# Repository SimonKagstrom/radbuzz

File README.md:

# Radbuzz
Radbuzz is an infotainment and trip computer for electric mopeds and motorcycles, targeting VESC-based
controllers. It's built for an ESP32P4 microcontroller, but can also be run on the desktop for testing.

<p align="center">

</p>
<p align="center">

</p>
<p align="center">

</p>
<p align="center">

</p>

Features:

* OpenStreetMap-based map (currently OpenCycleMap) with different zoom levels, via a GPS module
* Supports receiving Google maps/OsmAnd/etc navigation instructions via the [Gadgetbridge](https://github.com/Freeyourgadget/Gadgetbridge) app
* Speedometer, both based on VESC data and GPS
* Trip data, with average consumption, distance etc
* Tesla-style power meter bar on the right
* Trip log shown on the map, with power indicator in color
* Range estimation shown on the map
* BMS status via BLE (currently em3ev KingShark/Ali new energy BMSes)
* Incoming phone calls can accepted/declined
* SMS:es and emails are forwarded from the phone
* A menu for configuration
* Written in clean and modern C++ (C++23)

Hardware:

* [Waveshare 4.3" ESP32P4 Touch](https://www.waveshare.com/product/arduino/boards-kits/esp32-p4/esp32-p4-wifi6-touch-lcd-4.3.htm)
* A rotary encoder
* UART-based GPS (UBLOX Neo-6M / Neo-7M tested)
* A CAN-bus adapter to communicate with the VESC (a Waveshare SN65HVD230 has been used)
* A DC/DC converter to power the ESP32P4 from the 12V outlet on the VESC (a [Waveshare DC-DC buck mini module](https://www.waveshare.com/dc5-36-to-dc3v3-5.htm) used here)

the pinout for the ESP32P4 can be seen in [waveshare_p4_touch_4_3/main.cc](esp32/waveshare_p4_touch_4_3/main/main.cc)

## Setup
First install the `eim` tool (the esp-idf installation manager).

```
eim install -i v6.1
source $HOME/.espressif/tools/activate_idf_v6.1.sh
npm i lv_font_conv -g
pip3 install jinja2 pyyaml
```

## Build (target)
```
cmake -GNinja -B radbuzz_waveshare_p4_touch_4_3 -DCMAKE_BUILD_TYPE=Release <path>/radbuzz/esp32/waveshare_p4_touch_4_3
cmake --build radbuzz_waveshare_p4_touch_4_3
```

And then flash with

```
cd radbuzz_waveshare_p4_touch_4_3
ninja flash   # Or idf.py flash
```

## Build (qt/unittest)
Install the same lvgl/Python dependencies as on target:

```
npm i lv_font_conv -g
pip3 install jinja2 pyyaml
```

And then:

```
cmake -GNinja -B radbuzz_qt <path>/radbuzz/qt
cmake --build radbuzz_qt
```

or

```
cmake -GNinja -B radbuzz_unittest <path>/radbuzz/test/unittest/
cmake --build radbuzz_unittest
```

See [doc/build_instructions.md](doc/build_instructions.md) for more details on building and flashing the C6
firmware for wifi/Bluetooth.

## The OSM API key
Get an API key for thunderforest via https://www.thunderforest.com/docs/apikeys/

Put this key as a plain string in an `osm_api_key.txt` file in the root directory of this
project, to build it into the firmware.

A key can also be placed on the SD card, as `app_data/osm_key.txt`, which will be
preferred over the build time one if it exists. It's JSON:

```json
{"api_key": "0123456789abcdef"}
```

## Wifi SSID
Store the SSIDs and passwords as JSON in an `app_data/ssid.txt` file on the SD card. E.g.,

```json
{
  "networks": [
    {"ssid": "MySsid", "password": "PasswordForMySsid"},
    {"ssid": "OtherSsid", "password": "PasswordForOtherSsid"},
    {"ssid": "OpenCafeSsid"}
  ]
}
```

Leave out the password for open networks. The networks are stored on the
board, and the file is only imported again when its contents change.

## Trip upload
Trips are uploaded to a [Traccar](https://www.traccar.org/) server with the OsmAnd protocol,
configured with a JSON `app_data/traccar.txt` file on the SD card:

```json
{"url": "https://host.tailnet.ts.net", "id": "device-id", "demo_id": "demo-device-id"}
```

The `demo_id` is optional, and demo trips are only uploaded with it. Like `ssid.txt`, the file
is stored on the board and only imported again when it changes.

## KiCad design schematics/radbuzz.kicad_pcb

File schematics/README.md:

## Setup for the mock script
```
pip3 install manifold3d trimesh matplotlib
```

## Generate a step file for import into onshape

```
kicad-cli pcb export step --subst-models \
    --component-filter "J1,J2,J3,J4,J5,J6,U2,C3,C14,C15,C16,C17" \
    --user-origin 42.775x113.55mm \
    -f -o radbuzz.step radbuzz.kicad_pcb
```

The component filter has no way to exclude a part, so the parts to include are
listed. J9 is left out, since it is the GPS module's header.

For the encoder board:

```
kicad-cli pcb export step --subst-models \
    --user-origin 36.25x76mm \
    -f -o encoder_board.step encoder_board/encoder_board.kicad_pcb
```

KiCad has no 3D model for the EC11E encoder, so the step file has only the
board and its connector, and kicad-cli warns about the missing model.

The user origin is the lower left corner of each board.

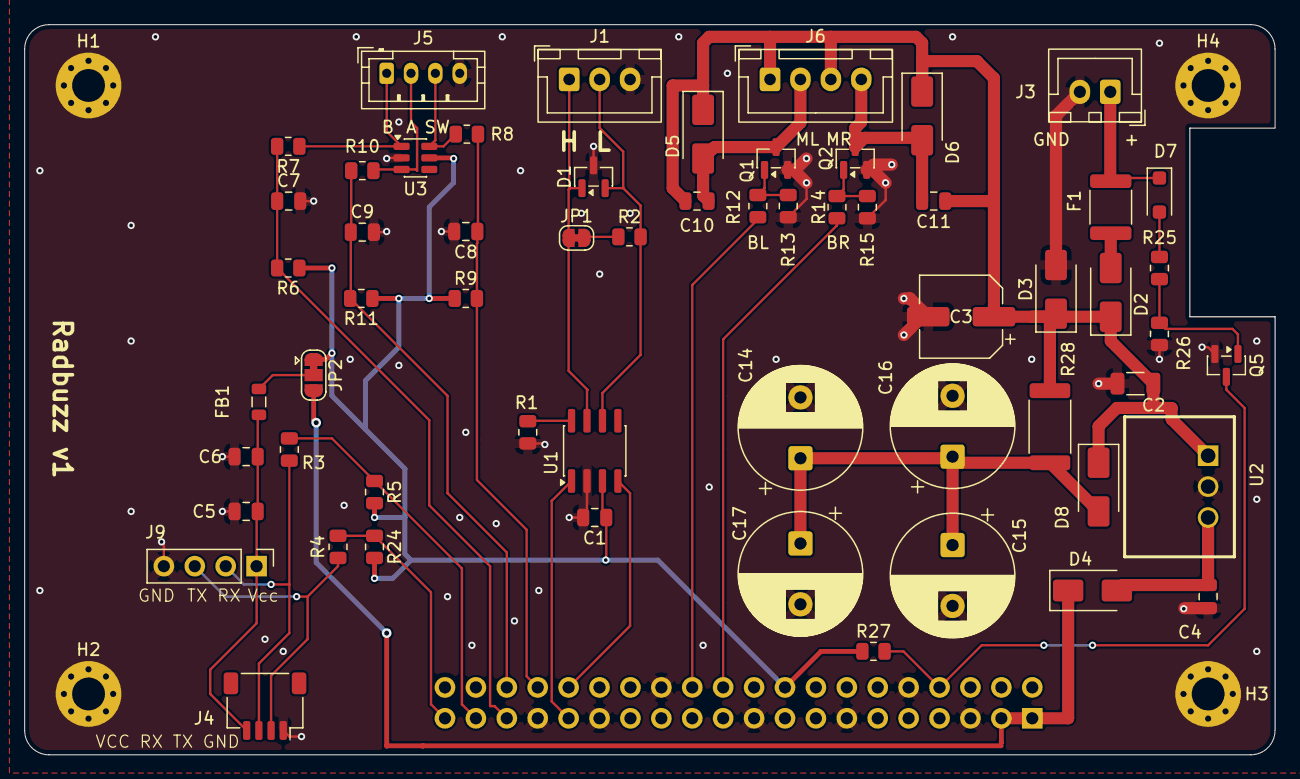
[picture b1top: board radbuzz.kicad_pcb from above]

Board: 2 copper layers, 102.8 x 60.0 mm, 64 parts (1 on the bottom side), 35 nets.

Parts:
C1, C6, C10, C11: 100nF; C_0805_2012Metric
C2: 10µF/50V X5R; C_1206_3216Metric
C3: 47µF/35V; CP_Elec_6.3x7.7
C4, C5: 22µF/25V X5R; C_0805_2012Metric
C7, C8, C9: 10nF; C_0805_2012Metric
C14, C15, C16, C17: 1000µF/35V; CP_Radial_D10.0mm_P5.00mm
D1: NUP2105L; SOT-23
D2, D4: SS34; D_SMA
D3: SMAJ15A; D_SMA
D5, D6, D8: SS14; D_SMA
D7: BZT52C9V1; D_SOD-123F
F1: Polyfuse 1.5A/24V; Fuse_1812_4532Metric
FB1: 600Ω@100MHz; L_0805_2012Metric
H1, H2, H3, H4: MountingHole_Pad; MountingHole_2.7mm_M2.5_Pad_Via
J1: CAN; JST_XH_B3B-XH-A_1x03_P2.50mm_Vertical
J2: BOARD; PinHeader_2x20_P2.54mm_Vertical
J3: POWER; JST_XH_B2B-XH-A_1x02_P2.50mm_Vertical
J4: GPS; JST_SH_SM04B-SRSS-TB_1x04-1MP_P1.00mm_Horizontal
J5: ROTARY_ENCODER; JST_PH_B4B-PH-K_1x04_P2.00mm_Vertical
J6: MOTOR; JST_XH_B4B-XH-A_1x04_P2.50mm_Vertical
J9: Conn_01x04_Pin; PinHeader_1x04_P2.54mm_Vertical
JP1: SolderJumper_2_Bridged; SolderJumper-2_P1.3mm_Bridged_RoundedPad1.0x1.5mm
JP2: SolderJumper_3_Bridged12; SolderJumper-3_P1.3mm_Bridged12_RoundedPad1.0x1.5mm
Q1, Q2: AO3400A; SOT-23
Q5: MMBT3904; SOT-23
R1, R5, R6, R9, R11, R24, R25, R27: 10k; R_0805_2012Metric
R2: 120Ω; R_0805_2012Metric
R3, R4: 220Ω; R_0805_2012Metric
R7, R8, R10: 1k; R_0805_2012Metric
R12, R14: 100Ω; R_0805_2012Metric
R13, R15: 100k; R_0805_2012Metric
R26: 4k7; R_0805_2012Metric
R28: 10Ω; R_2512_6332Metric
U1: SN65HVD230; SOIC-8_3.9x4.9mm_P1.27mm
U2: K7805-2000R3
U3: SRV05-4; SOT-23-6

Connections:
+3V3: C1.1, J2.18, JP2.1 (A), R5.2, R6.1, R9.1, R11.1, R24.2, R27.1, U1.3 (VCC), U3.5 (VP)
+5V: D4.1 (K), J2.1, J2.3, JP2.3 (B)
+12V: C2.1, C3.1, C10.1, C11.1, D2.1 (K), D3.1 (A1), D5.1 (K), D6.1 (K), D8.1 (K), J6.1, J6.3, R28.1, U2.1 (Vin)
/Buzzer motor handling/MOTOR_L_N: C10.2, D5.2 (A), J6.2, Q1.3 (D)
/Buzzer motor handling/MOTOR_R_N: C11.2, D6.2 (A), J6.4, Q2.3 (D)
/Power/5V_PRE: C4.1, D4.2 (A), U2.3 (Vout)
/Power/HOLDUP: C14.1, C15.1, C16.1, C17.1, D8.2 (A), R28.2
/Power/VIN_FUSED: D2.2 (A), F1.2
/Power/VIN_RAW: D7.1 (K), F1.1, J3.1
BUZZ_L: J2.24, R12.2
BUZZ_R: J2.22, R14.2
CAN_RX: J2.32, U1.4 (R)
CAN_TX: J2.31, U1.1 (D)
ENC_A: C9.1, J2.36, R10.2, R11.2
ENC_B: C7.1, J2.35, R6.2, R7.2
ENC_SW: C8.1, J2.34, R8.2, R9.2
FROM_GPS: J2.39, R4.2, R24.1
GND: C1.2, C2.2, C3.2, C4.2, C5.2, C6.2, C7.2, C8.2, C9.2, C14.2, C15.2, C16.2, C17.2, D1.3 (A), D3.2 (A2), H1.1 (1_1), H2.1 (1_1), H3.1 (1_1), H4.1 (1_1), J1.3, J2.5, J2.10, J2.13, J2.19, J2.26, J2.29, J2.33, J2.40, J3.2, J4.1, J5.4, J9.4, Q1.2 (S), Q2.2 (S), Q5.2 (E), R1.2, R13.1, R15.1, R26.2, U1.2 (GND), U2.2 (GND), U3.2 (VN)
unnamed: D7.2 (A), R25.1
unnamed: D1.1 (K), J1.1, JP1.1 (A), U1.7 (CANH)
unnamed: D1.2 (K), J1.2, R2.2, U1.6 (CANL)
unnamed: J4.2, J9.3, R4.1
unnamed: J4.3, J9.2, R3.1
unnamed: C5.1, C6.1, FB1.2, J4.4, J9.1
unnamed: J5.1, R7.1, U3.1 (IO1)
unnamed: J5.2, R10.1, U3.3 (IO2)
unnamed: J5.3, R8.1, U3.6 (IO4)
unnamed: JP1.2 (B), R2.1
unnamed: FB1.1, JP2.2 (C)
unnamed: Q1.1 (G), R12.1, R13.2
unnamed: Q2.1 (G), R14.1, R15.2
unnamed: Q5.1 (B), R25.2, R26.1
unnamed: R1.1, U1.8 (Rs)
PWR_FAIL: J2.8, Q5.3 (C), R27.2
TO_GPS: J2.37, R3.2, R5.1
